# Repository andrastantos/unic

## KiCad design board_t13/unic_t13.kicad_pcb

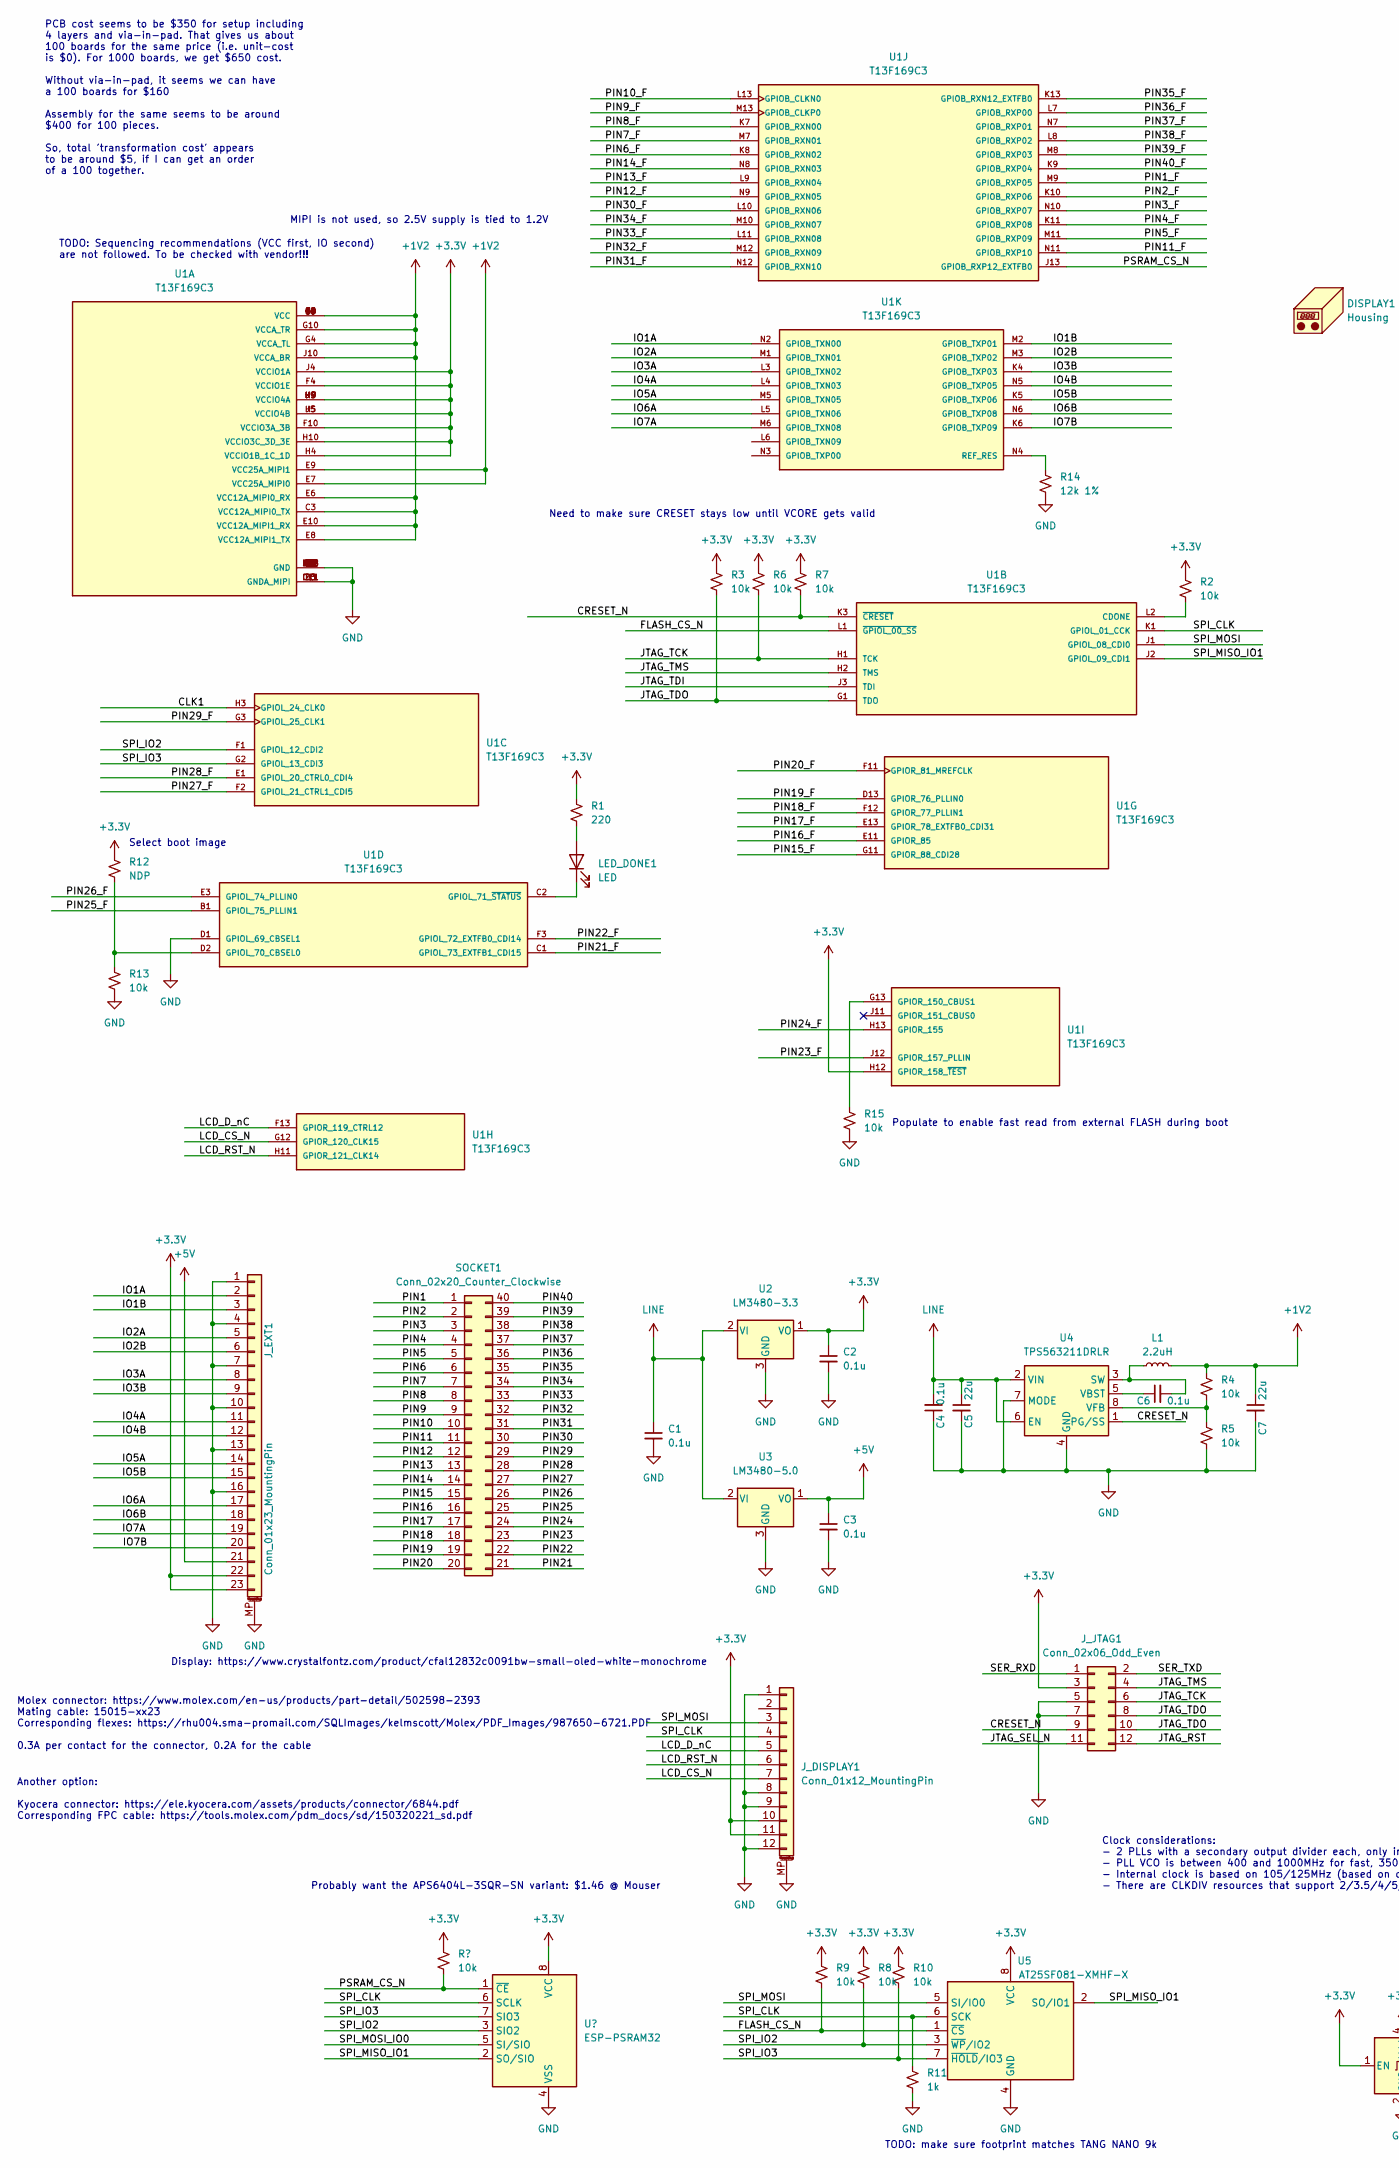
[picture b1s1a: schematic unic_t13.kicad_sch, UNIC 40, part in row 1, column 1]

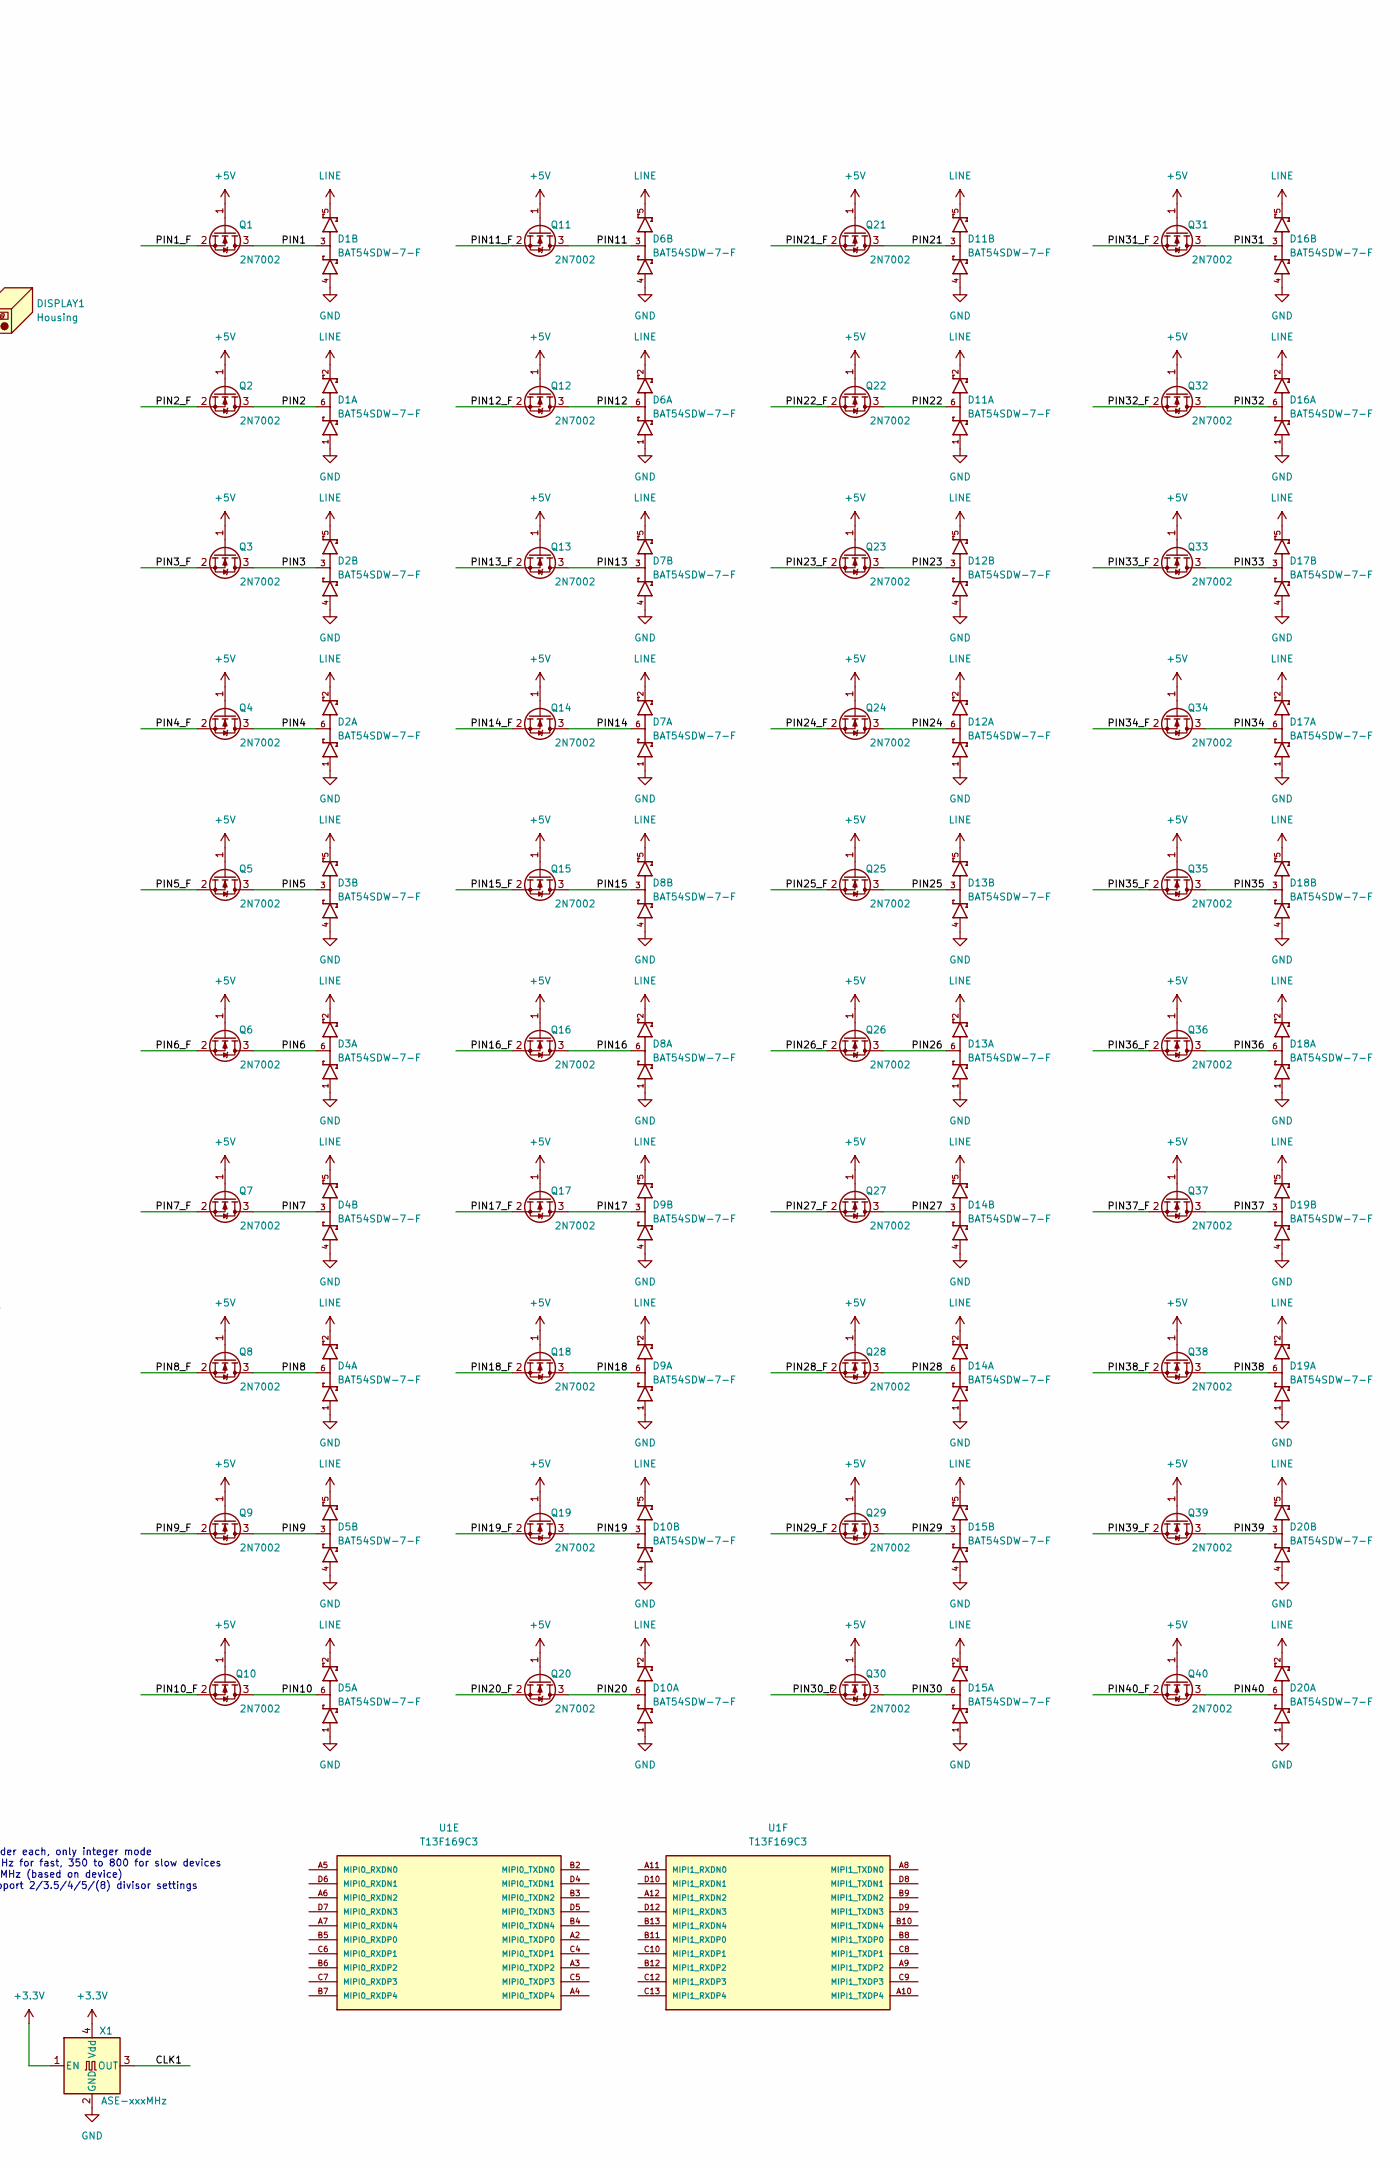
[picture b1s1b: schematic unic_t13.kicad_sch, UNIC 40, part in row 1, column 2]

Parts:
C1, C2, C3, C4, C6: 0.1u; C_0402_1005Metric_Pad0.74x0.62mm_HandSolder
C5, C7: 22u; C_0805_2012Metric_Pad1.18x1.45mm_HandSolder
D1, D2, D3, D4, D5, D6, D7, D8, D9, D10, D11, D12, D13, D14, D15, D16, D17, D18, D19, D20: BAT54SDW-7-F; SOT65P210X110-6N; PARTREV 17 - 2
DISPLAY1: Housing; CFAL12832C-0091B-W_A
J_DISPLAY1: Conn_01x12_MountingPin; CF31121D0R0-05-NH
J_EXT1: Conn_01x23_MountingPin; Molex_502598-2393_2Rows-23Pins-1MP_P0.60mm_Horizontal
J_JTAG1: Conn_02x06_Odd_Even; PinHeader_2x06_P1.27mm_Vertical_SMD
L1: 2.2uH; L_1008_2520Metric_Pad1.43x2.20mm_HandSolder
LED_DONE1: LED; LED_0402_1005Metric_Pad0.77x0.64mm_HandSolder
Q1, Q2, Q3, Q4, Q5, Q6, Q7, Q8, Q9, Q10, Q11, Q12, Q13, Q14, Q15, Q16, Q17, Q18, Q19, Q20, Q21, Q22, Q23, Q24, Q25, Q26, Q27, Q28, Q29, Q30, Q31, Q32, Q33, Q34, Q35, Q36, Q37, Q38, Q39, Q40: 2N7002; Diodes_DFN1006-3
R1: 220; R_0402_1005Metric_Pad0.72x0.64mm_HandSolder
R2, R3, R4, R5, R6, R7, R8, R9, R10, R13, R15: 10k; R_0402_1005Metric_Pad0.72x0.64mm_HandSolder
R11: 1k; R_0402_1005Metric_Pad0.72x0.64mm_HandSolder
R12: NDP; R_0402_1005Metric_Pad0.72x0.64mm_HandSolder
R14: 12k 1%; R_0402_1005Metric_Pad0.72x0.64mm_HandSolder
SOCKET1: Conn_02x20_Counter_Clockwise; DIP-40_pin_header
U1: T13F169C3; BGA169C65P13X13_900X900X100; PARTREV v3.3
U2: LM3480-3.3; SOT-23
U3: LM3480-5.0; SOT-23
U4: TPS563211DRLR; SOT-583
U5: AT25SF081-XMHF-X; TSSOP-8_4.4x3mm_P0.65mm
X1: ASE-xxxMHz; Oscillator_SMD_Abracon_ASE-4Pin_3.2x2.5mm

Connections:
+1V2: C7.1, L1.2, R4.1, U1.C3 (VCC12A_MIPI0_TX), U1.E4 (VCC), U1.E6 (VCC12A_MIPI0_RX), U1.E7 (VCC25A_MIPI0), U1.E8 (VCC12A_MIPI1_TX), U1.E9 (VCC25A_MIPI1), U1.E10 (VCC12A_MIPI1_RX), U1.F7 (VCC), U1.F9 (VCC), U1.G4 (VCCA_TL), U1.G5 (VCC), U1.G8 (VCC), U1.G9 (VCC), U1.G10 (VCCA_TR), U1.H6 (VCC), U1.J6 (VCC), U1.J10 (VCCA_BR)
+3V3: C2.1, J_DISPLAY1.10, J_DISPLAY1.11, J_EXT1.22, J_EXT1.23, J_JTAG1.3, R1.1, R2.1, R3.1, R6.1, R7.1, R8.1, R9.1, R10.1, R12.1, U1.F4 (VCCIO1E), U1.F10 (VCCIO3A_3B), U1.H4 (VCCIO1B_1C_1D), U1.H5 (VCCIO4B), U1.H7 (VCCIO4A), U1.H8 (VCCIO4A), U1.H9 (VCCIO4A), U1.H10 (VCCIO3C_3D_3E), U1.H12 (GPIOR_158_~TEST), U1.J4 (VCCIO1A), U1.J5 (VCCIO4B), U1.J9 (VCCIO4A), U2.1 (VO), U5.8 (VCC), X1.1 (EN), X1.4 (Vdd)
+5V: C3.1, J_EXT1.21, Q1.1 (G), Q2.1 (G), Q3.1 (G), Q4.1 (G), Q5.1 (G), Q6.1 (G), Q7.1 (G), Q8.1 (G), Q9.1 (G), Q10.1 (G), Q11.1 (G), Q12.1 (G), Q13.1 (G), Q14.1 (G), Q15.1 (G), Q16.1 (G), Q17.1 (G), Q18.1 (G), Q19.1 (G), Q20.1 (G), Q21.1 (G), Q22.1 (G), Q23.1 (G), Q24.1 (G), Q25.1 (G), Q26.1 (G), Q27.1 (G), Q28.1 (G), Q29.1 (G), Q30.1 (G), Q31.1 (G), Q32.1 (G), Q33.1 (G), Q34.1 (G), Q35.1 (G), Q36.1 (G), Q37.1 (G), Q38.1 (G), Q39.1 (G), Q40.1 (G), U3.1 (VO)
/CLK1: U1.H3 (GPIOL_24_CLK0), X1.3 (OUT)
/CRESET_N: J_JTAG1.9, R7.2, U1.K3 (~CRESET), U4.1 (PG/SS)
/FLASH_CS_N: R9.2, U1.L1 (~GPIOL_00_SS), U5.1 (~CS)
/FLASH_IO2: R8.2, U1.F1 (GPIOL_12_CDI2), U5.3 (~WP/IO2)
/FLASH_IO3: R10.2, U1.G2 (GPIOL_13_CDI3), U5.7 (~HOLD/IO3)
/FLASH_MISO_IO1: U1.J2 (GPIOL_09_CDI1), U5.2 (SO/IO1)
/IO1A: J_EXT1.2, U1.N2 (GPIOB_TXN00)
/IO1B: J_EXT1.3, U1.M2 (GPIOB_TXP01)
/IO2A: J_EXT1.5, U1.M1 (GPIOB_TXN01)
/IO2B: J_EXT1.6, U1.M3 (GPIOB_TXP02)
/IO3A: J_EXT1.8, U1.L3 (GPIOB_TXN02)
/IO3B: J_EXT1.9, U1.K4 (GPIOB_TXP03)
/IO4A: J_EXT1.11, U1.L4 (GPIOB_TXN03)
/IO4B: J_EXT1.12, U1.N5 (GPIOB_TXP05)
/IO5A: J_EXT1.14, U1.M5 (GPIOB_TXN05)
/IO5B: J_EXT1.15, U1.K5 (GPIOB_TXP06)
/IO6A: J_EXT1.17, U1.L5 (GPIOB_TXN06)
/IO6B: J_EXT1.18, U1.N6 (GPIOB_TXP08)
/IO7A: J_EXT1.19, U1.M6 (GPIOB_TXN08)
/IO7B: J_EXT1.20, U1.K6 (GPIOB_TXP09)
/JTAG_RST: J_JTAG1.12
/JTAG_SEL_N: J_JTAG1.11
/JTAG_TCK: J_JTAG1.6, R6.2, U1.H1 (TCK)
/JTAG_TDI: U1.J3 (TDI)
/JTAG_TDO: J_JTAG1.8, J_JTAG1.10, R3.2, U1.G1 (TDO)
/JTAG_TMS: J_JTAG1.4, U1.H2 (TMS)
/LCD_CS_N: J_DISPLAY1.7, U1.G12 (GPIOR_120_CLK15)
/LCD_D_nC: J_DISPLAY1.5, U1.F13 (GPIOR_119_CTRL12)
/LCD_RST_N: J_DISPLAY1.6, U1.H11 (GPIOR_121_CLK14)
/PIN1: D1.3, Q1.3 (D), SOCKET1.1
/PIN1_F: Q1.2 (S), U1.M9 (GPIOB_RXP05)
/PIN2: D1.6, Q2.3 (D), SOCKET1.2
/PIN2_F: Q2.2 (S), U1.K10 (GPIOB_RXP06)
/PIN3: D2.3, Q3.3 (D), SOCKET1.3
/PIN3_F: Q3.2 (S), U1.N10 (GPIOB_RXP07)
/PIN4: D2.6, Q4.3 (D), SOCKET1.4
/PIN4_F: Q4.2 (S), U1.K11 (GPIOB_RXP08)
/PIN5: D3.3, Q5.3 (D), SOCKET1.5
/PIN5_F: Q5.2 (S), U1.M11 (GPIOB_RXP09)
/PIN6: D3.6, Q6.3 (D), SOCKET1.6
/PIN6_F: Q6.2 (S), U1.K8 (GPIOB_RXN02)
/PIN7: D4.3, Q7.3 (D), SOCKET1.7
/PIN7_F: Q7.2 (S), U1.M7 (GPIOB_RXN01)
/PIN8: D4.6, Q8.3 (D), SOCKET1.8
/PIN8_F: Q8.2 (S), U1.K7 (GPIOB_RXN00)
/PIN9: D5.3, Q9.3 (D), SOCKET1.9
/PIN9_F: Q9.2 (S), U1.M13 (GPIOB_CLKP0)
/PIN10: D5.6, Q10.3 (D), SOCKET1.10
/PIN10_F: Q10.2 (S), U1.L13 (GPIOB_CLKN0)
/PIN11: D6.3, Q11.3 (D), SOCKET1.11
/PIN11_F: Q11.2 (S), U1.N11 (GPIOB_RXP10)
/PIN12: D6.6, Q12.3 (D), SOCKET1.12
/PIN12_F: Q12.2 (S), U1.N9 (GPIOB_RXN05)
/PIN13: D7.3, Q13.3 (D), SOCKET1.13
/PIN13_F: Q13.2 (S), U1.L9 (GPIOB_RXN04)
/PIN14: D7.6, Q14.3 (D), SOCKET1.14
/PIN14_F: Q14.2 (S), U1.N8 (GPIOB_RXN03)
/PIN15: D8.3, Q15.3 (D), SOCKET1.15
/PIN15_F: Q15.2 (S), U1.G11 (GPIOR_88_CDI28)
/PIN16: D8.6, Q16.3 (D), SOCKET1.16
/PIN16_F: Q16.2 (S), U1.E11 (GPIOR_85)
/PIN17: D9.3, Q17.3 (D), SOCKET1.17
/PIN17_F: Q17.2 (S), U1.E13 (GPIOR_78_EXTFB0_CDI31)
/PIN18: D9.6, Q18.3 (D), SOCKET1.18
/PIN18_F: Q18.2 (S), U1.F12 (GPIOR_77_PLLIN1)
/PIN19: D10.3, Q19.3 (D), SOCKET1.19
/PIN19_F: Q19.2 (S), U1.D13 (GPIOR_76_PLLIN0)
/PIN20: D10.6, Q20.3 (D), SOCKET1.20
/PIN20_F: Q20.2 (S), U1.F11 (GPIOR_81_MREFCLK)
/PIN21: D11.3, Q21.3 (D), SOCKET1.21
/PIN21_F: Q21.2 (S), U1.C1 (GPIOL_73_EXTFB1_CDI15)
/PIN22: D11.6, Q22.3 (D), SOCKET1.22
/PIN22_F: Q22.2 (S), U1.F3 (GPIOL_72_EXTFB0_CDI14)
/PIN23: D12.3, Q23.3 (D), SOCKET1.23
/PIN23_F: Q23.2 (S), U1.J12 (GPIOR_157_PLLIN)
/PIN24: D12.6, Q24.3 (D), SOCKET1.24
/PIN24_F: Q24.2 (S), U1.H13 (GPIOR_155)
/PIN25: D13.3, Q25.3 (D), SOCKET1.25
/PIN25_F: Q25.2 (S), U1.B1 (GPIOL_75_PLLIN1)
/PIN26: D13.6, Q26.3 (D), SOCKET1.26
/PIN26_F: Q26.2 (S), U1.E3 (GPIOL_74_PLLIN0)
/PIN27: D14.3, Q27.3 (D), SOCKET1.27
/PIN27_F: Q27.2 (S), U1.F2 (GPIOL_21_CTRL1_CDI5)
/PIN28: D14.6, Q28.3 (D), SOCKET1.28
/PIN28_F: Q28.2 (S), U1.E1 (GPIOL_20_CTRL0_CDI4)
/PIN29: D15.3, Q29.3 (D), SOCKET1.29
/PIN29_F: Q29.2 (S), U1.G3 (GPIOL_25_CLK1)
/PIN30: D15.6, Q30.3 (D), SOCKET1.30
/PIN30_F: Q30.2 (S), U1.L10 (GPIOB_RXN06)
/PIN31: D16.3, Q31.3 (D), SOCKET1.31
/PIN31_F: Q31.2 (S), U1.N12 (GPIOB_RXN10)
/PIN32: D16.6, Q32.3 (D), SOCKET1.32
/PIN32_F: Q32.2 (S), U1.M12 (GPIOB_RXN09)
/PIN33: D17.3, Q33.3 (D), SOCKET1.33
/PIN33_F: Q33.2 (S), U1.L11 (GPIOB_RXN08)
/PIN34: D17.6, Q34.3 (D), SOCKET1.34
/PIN34_F: Q34.2 (S), U1.M10 (GPIOB_RXN07)
/PIN35: D18.3, Q35.3 (D), SOCKET1.35
/PIN35_F: Q35.2 (S), U1.K13 (GPIOB_RXN12_EXTFB0)
/PIN36: D18.6, Q36.3 (D), SOCKET1.36
/PIN36_F: Q36.2 (S), U1.L7 (GPIOB_RXP00)
/PIN37: D19.3, Q37.3 (D), SOCKET1.37
/PIN37_F: Q37.2 (S), U1.N7 (GPIOB_RXP01)
/PIN38: D19.6, Q38.3 (D), SOCKET1.38
/PIN38_F: Q38.2 (S), U1.L8 (GPIOB_RXP02)
/PIN39: D20.3, Q39.3 (D), SOCKET1.39
/PIN39_F: Q39.2 (S), U1.M8 (GPIOB_RXP03)
/PIN40: D20.6, Q40.3 (D), SOCKET1.40
/PIN40_F: Q40.2 (S), U1.K9 (GPIOB_RXP04)
/SER_RXD: J_JTAG1.1
/SER_TXD: J_JTAG1.2
/SPI_CLK: J_DISPLAY1.4, R11.1, U1.K1 (GPIOL_01_CCK), U5.6 (SCK)
/SPI_MOSI: J_DISPLAY1.3, U1.J1 (GPIOL_08_CDI0), U5.5 (SI/IO0)
GND: C1.2, C2.2, C3.2, C4.1, C5.2, C7.2, D1.1, D1.4, D2.1, D2.4, D3.1, D3.4, D4.1, D4.4, D5.1, D5.4, D6.1, D6.4, D7.1, D7.4, D8.1, D8.4, D9.1, D9.4, D10.1, D10.4, D11.1, D11.4, D12.1, D12.4, D13.1, D13.4, D14.1, D14.4, D15.1, D15.4, D16.1, D16.4, D17.1, D17.4, D18.1, D18.4, D19.1, D19.4, D20.1, D20.4, J_DISPLAY1.1, J_DISPLAY1.8, J_DISPLAY1.9, J_DISPLAY1.12, J_DISPLAY1.MP (MountPin), J_EXT1.1, J_EXT1.4, J_EXT1.7, J_EXT1.10, J_EXT1.13, J_EXT1.16, J_EXT1.MP (MountPin), J_JTAG1.5, J_JTAG1.7, R5.2, R11.2, R13.2, R14.2, R15.2, U1.A1 (GND), U1.A13 (GND), U1.C11 (GNDA_MIPI), U1.D1 (GPIOL_69_CBSEL1), U1.D3 (GNDA_MIPI), U1.D11 (GNDA_MIPI), U1.E2 (GND), U1.E5 (GNDA_MIPI), U1.E12 (GND), U1.F5 (GND), U1.F6 (GND), U1.F8 (GND), U1.G6 (GND), U1.G7 (GND), U1.J7 (GND), U1.J8 (GND), U1.K2 (GND), U1.K12 (GND), U1.L12 (GND), U1.M4 (GND), U1.N1 (GND), U1.N13 (GND), U2.3 (GND), U3.3 (GND), U4.4 (GND), U4.7 (MODE), U5.4 (GND), X1.2 (GND)
LINE: C1.1, C4.2, C5.1, D1.2, D1.5, D2.2, D2.5, D3.2, D3.5, D4.2, D4.5, D5.2, D5.5, D6.2, D6.5, D7.2, D7.5, D8.2, D8.5, D9.2, D9.5, D10.2, D10.5, D11.2, D11.5, D12.2, D12.5, D13.2, D13.5, D14.2, D14.5, D15.2, D15.5, D16.2, D16.5, D17.2, D17.5, D18.2, D18.5, D19.2, D19.5, D20.2, D20.5, U2.2 (VI), U3.2 (VI), U4.2 (VIN), U4.6 (EN)
unnamed: C6.1, U4.5 (VBST)
unnamed: C6.2, L1.1, U4.3 (SW)
unnamed: LED_DONE1.2 (A), R1.2
unnamed: R4.2, R5.1, U4.8 (VFB)
unnamed: LED_DONE1.1 (K), U1.C2 (GPIOL_71_~STATUS)
unnamed: R12.2, R13.1, U1.D2 (GPIOL_70_CBSEL0)
unnamed: R15.1, U1.G13 (GPIOR_150_CBUS1)
unnamed: R2.2, U1.L2 (CDONE)
unnamed: R14.1, U1.N4 (REF_RES)

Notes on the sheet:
Populate to enable fast read from external FLASH during boot
PCB cost seems to be $350 for setup including 4 layers and via-in-pad. That gives us about 100 boards for the same price (i.e. unit-cost is $0). For 1000 boards, we get $650 cost. Without via-in-pad, it seems we can have a 100 boards for $160 Assembly for the same seems to be around $400 for 100 pi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
Molex connector: https://www.molex.com/en-us/products/part-detail/502598-2393 Mating cable: 15015-xx23 Corresponding flexes: https://rhu004.sma-promail.com/SQLImages/kelmscott/Molex/PDF_Images/987650-6721.PDF 0.3A per contact for the connector, 0.2A for the cable
Another option: Kyocera connector: https://ele.kyocera.com/assets/products/connector/6844.pdf Corresponding FPC cable: https://tools.molex.com/pdm_docs/sd/150320221_sd.pdf
Clock considerations: - 2 PLLs with a secondary output divider each, only integer mode - PLL VCO is between 400 and 1000MHz for fast, 350 to 800 for slow devices - Internal clock is based on 105/125MHz (based on device) - There are CLKDIV resources that support 2/3.5/4/5/(8) divisor settings
Select boot image
TODO: Sequencing recommendations (VCC first, IO second) are not followed. To be checked with vendor!!!
Need to make sure CRESET stays low until VCORE gets valid
Probably want the APS6404L-3SQR-SN variant: $1.46 @ Mouser
TODO: make sure footprint matches TANG NANO 9k
Display: https://www.crystalfontz.com/product/cfal12832c0091bw-small-oled-white-monochrome
MIPI is not used, so 2.5V supply is tied to 1.2V

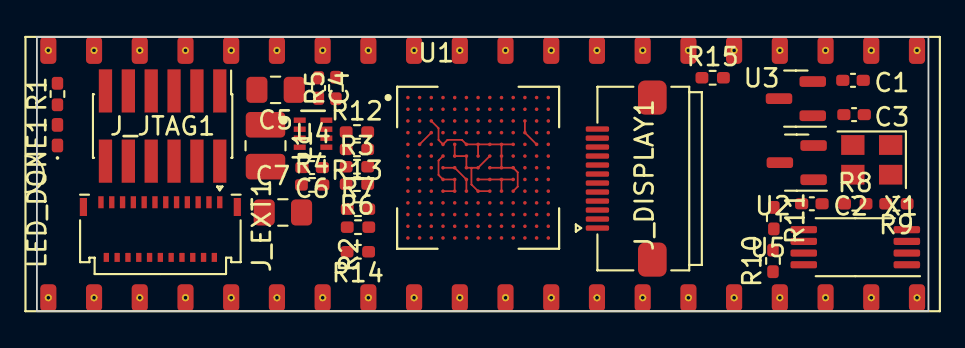
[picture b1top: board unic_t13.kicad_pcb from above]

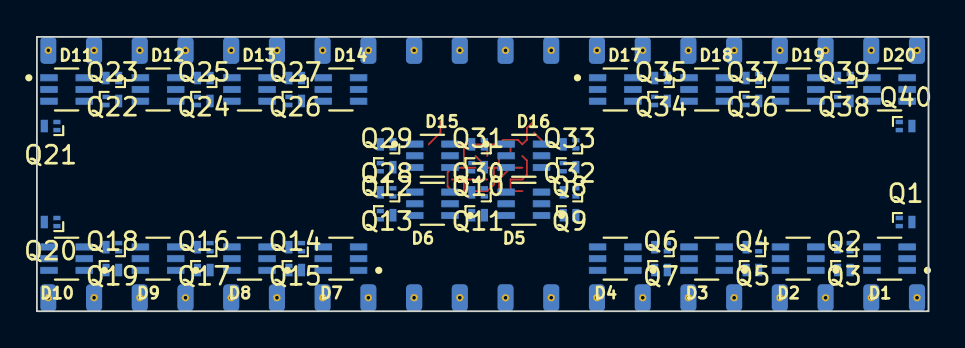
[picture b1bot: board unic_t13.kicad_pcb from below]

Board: 4 copper layers, 49.5 x 15.2 mm, 96 parts (60 on the bottom side), 122 nets.

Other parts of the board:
DISPLAY1#2: Housing; CFAL12832C-0091B-W_A

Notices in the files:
devel_gw1/devel_gw1.kicad_pcb:
(C) 2024 Andras Tantos &
